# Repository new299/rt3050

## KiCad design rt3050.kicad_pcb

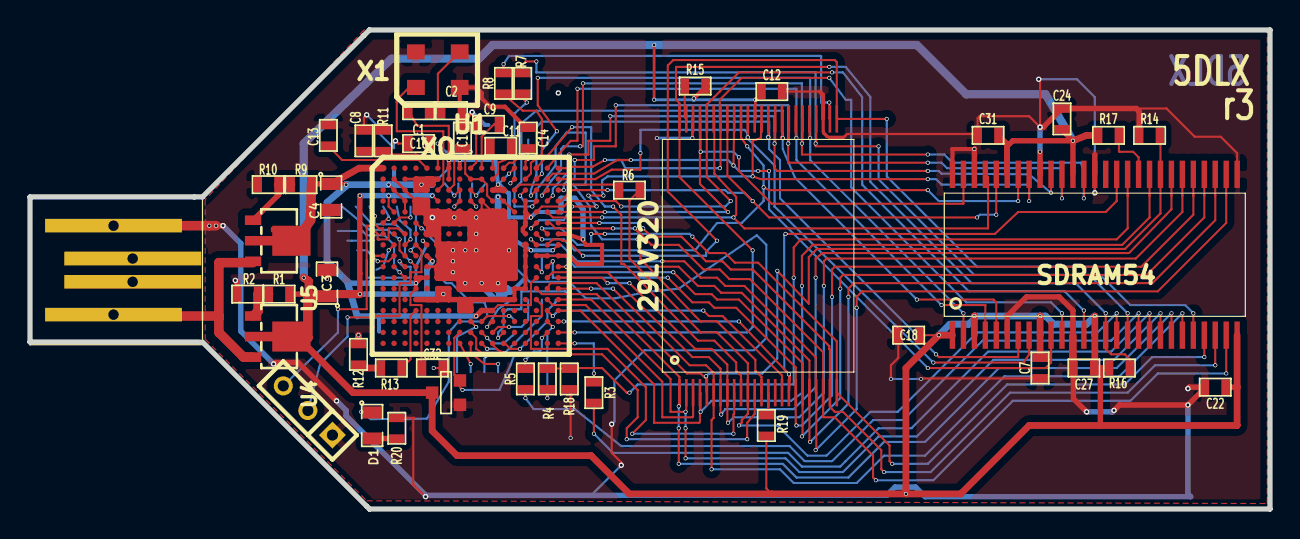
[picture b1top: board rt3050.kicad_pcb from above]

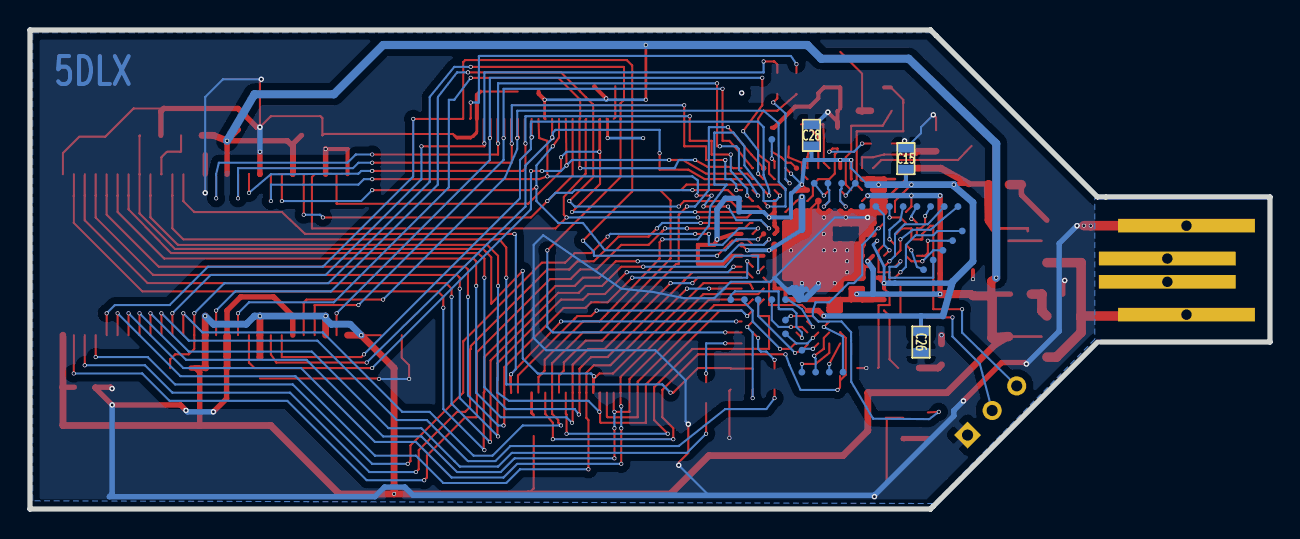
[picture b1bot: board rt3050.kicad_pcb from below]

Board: 2 copper layers, 90.6 x 35.0 mm, 60 parts (11 on the bottom side), 106 nets.

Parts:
C1, C2, C7, C8, C9, C11, C12, C13, C14, C15, C16, C17, C18, C22, C24, C26, C27, C28, C31, C32: C; SM0603
C3, C4: C; SM0805
D1: LED; SM0805
J1: USB; USBEDGE
K1: CONN_SERIAL; SIL-3
P1: CONN_JTAG; smpad6
P2: CONN_RF; smpad4
P3, P7: CONN_1; smpad1
P4: CONN_SERIAL2; smpad8
P5: CONN_SPI; smpad4
P6: CONN_2; smpad2
P8: CONN_USB; smpads5
R1, R2, R9, R10, R11, R12, R13, R14, R15, R16, R17, R18, R19, R20: R; SM0603
R3, R5, R6, R7, R8: 36; SM0603
R4: 100; SM0603
U1: RT3050; TFBGA289
U2: 29LV320; TSOP48
U3: SDRAM54; TSOP54
U4, U5: LM1117; SOT89
U6: AIC809; SOT23GDS
X1: XO; SMD3225

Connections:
+1.2V: C4.1, C15.1, C26.1, C28.1, C32.1, R9.1, U1.A1, U1.A7, U1.A8, U1.A13, U1.B3, U1.B4, U1.B5, U1.B6, U1.B7, U1.C2, U1.C4, U1.C5, U1.C11, U1.C12, U1.D3, U1.D14, U1.E3, U1.E14, U1.F14, U1.G14, U1.G17, U1.H5, U1.J15, U1.J16, U1.J17, U1.L4, U1.L5, U1.L15, U1.M4, U1.P10, U1.P11, U5.2
+3.3V: C3.1, C7.1, C12.1, C18.1, C22.1, C24.1, C27.1, C31.1, R1.1, R15.2, R16.2, R17.1, R19.2, U1.D6, U1.D12, U1.E2, U1.E13, U1.H14, U1.H17, U1.J5, U1.J14, U1.K14, U1.L14, U1.M6, U1.M7, U1.M13, U1.M14, U1.N4, U1.N5, U1.N6, U1.N7, U1.N8, U1.N9, U1.N10, U1.N11, U1.N12, U1.N13, U1.P8, U1.P9, U2.37, U3.1, U3.3, U3.9, U3.14, U3.27, U3.43, U3.49, U4.2, U6.D
+5V: J1.1, U4.3, U5.3
GND: C2.2, C3.2, C4.2, C7.2, C8.2, C12.2, C13.2, C14.2, C15.2, C16.2, C17.2, C18.2, C22.2, C24.2, C26.2, C27.2, C28.2, C31.2, C32.2, J1.4, K1.1, P1.6, R2.2, R10.2, R11.2, R12.2, R14.1, R18.2, R20.2, U1.B2, U1.C3, U1.D4, U1.D5, U1.D10, U1.E4, U1.E5, U1.E6, U1.E7, U1.E8, U1.E9, U1.E10, U1.E11, U1.E12, U1.F5, U1.F6, U1.F7, U1.F8, U1.F9, U1.F10, U1.F11, U1.F12, U1.F13, U1.G5, U1.G6, U1.G9, U1.G10, U1.G11, U1.G12, U1.G13, U1.H6, U1.H7, U1.H8, U1.H9, U1.H10, U1.H11, U1.H12, U1.H13, U1.J6, U1.J7, U1.J8, U1.J9, U1.J10, U1.J11, U1.J12, U1.J13, U1.K5, U1.K6, U1.K7, U1.K8, U1.K9, U1.K10, U1.K11, U1.K12, U1.K13, U1.L6, U1.L7, U1.L8, U1.L9, U1.L10, U1.L11, U1.L12, U1.L13, U1.M8, U1.M9, U1.M10, U1.M11, U1.M12, U2.27, U2.46, U3.6, U3.12, U3.28, U3.41, U3.46, U3.52, U3.54, U6.G, X1.2, X1.4
unnamed: P1.5, U1.R11
unnamed: P4.3, U1.F2
unnamed: P1.3, U1.U11
unnamed: P1.1, U1.T12
unnamed: P4.7, U1.K4
unnamed: K1.3, U1.G3
unnamed: U1.C6, X1.1
unnamed: P8.1, U1.H2
unnamed: P4.5, U1.F1
unnamed: D1.2, R20.1
unnamed: C1.2, U1.C7
unnamed: P8.3, U1.J2
unnamed: P7.1, U1.U10
unnamed: P4.8, U1.J3
unnamed: P5.4, U1.R9
unnamed: P4.2, U1.J4
unnamed: P4.4, U1.H3
unnamed: P8.2, U1.K3
unnamed: P1.2, U1.U12
unnamed: P8.4, U1.J1
unnamed: P5.2, U1.T9
unnamed: K1.2, U1.H4
unnamed: P4.6, U1.G1
unnamed: D1.1, U1.F4
unnamed: P1.4, U1.T11
unnamed: P6.1, U1.R10
unnamed: P8.5, U1.L3
unnamed: C1.1, C2.1, X1.3
unnamed: P5.3, U1.U8
unnamed: P5.1, U1.U9
unnamed: P6.2, U1.T10
unnamed: R9.2, R10.1, U5.1
unnamed: R1.2, R2.1, U4.1
unnamed: U1.A17, U2.42, U3.11
unnamed: U1.K15, U2.20, U3.30
unnamed: U1.M17, U2.6, U3.22
unnamed: U1.E16, U2.43, U3.51
unnamed: U1.B17, U2.38, U3.8
unnamed: U1.D15, U2.33, U3.5
unnamed: R8.1, U2.26
unnamed: U1.D16, U2.34, U3.45
unnamed: U1.F17, U2.23, U3.25
unnamed: U1.L16, U2.7, U3.34
unnamed: U1.K16, U2.18, U3.32
unnamed: U1.H16, U2.25, U3.23
unnamed: R15.1, U2.47
unnamed: U1.F15, U2.36, U3.47
unnamed: U1.P16, U2.16
unnamed: R8.2, U1.B14
unnamed: U1.B15, U2.29, U3.2
unnamed: U1.N16, U2.3
unnamed: U1.N15, U2.9
unnamed: U1.E17, U2.45, U3.53
unnamed: R3.2, U1.U17
unnamed: R5.2, U1.T16
unnamed: R4.2, U1.R16
unnamed: U1.G15, U2.39, U3.48
unnamed: R6.2, U1.C13
unnamed: R7.2, U1.B13
unnamed: R3.1, U3.19
unnamed: R17.2, U3.37
unnamed: U1.A15, U2.10
unnamed: U1.C14, U2.13
unnamed: P3.1, U1.A14
unnamed: U1.A16, U2.31, U3.4
unnamed: U1.C15, U2.35, U3.7
unnamed: U1.B16, U2.40, U3.10
unnamed: U1.E15, U2.44, U3.13
unnamed: U1.G16, U2.24, U3.24
unnamed: U1.F16, U2.22, U3.26
unnamed: U1.K17, U2.19, U3.31
unnamed: U1.L17, U2.8, U3.33
unnamed: U1.R17, U2.17, U3.39
unnamed: R4.1, R18.1, U3.38
unnamed: U1.D17, U2.41, U3.50
unnamed: R14.2, U1.M16, U2.5, U3.35
unnamed: R5.1, U3.18
unnamed: U1.C16, U2.30, U3.42
unnamed: R7.1, U2.28, U3.17
unnamed: U1.N17, U2.2, U3.20
unnamed: R16.1, U1.T17, U2.48, U3.15
unnamed: R19.1, U2.14
unnamed: U1.P17, U2.4, U3.36
unnamed: U1.M15, U2.1, U3.21
unnamed: U1.C17, U2.32, U3.44
unnamed: R6.1, U2.11, U3.16
unnamed: U1.H15, U2.21, U3.29
unnamed: R12.1, R13.2
unnamed: R13.1, U1.P4
unnamed: C9.2, U1.A9
unnamed: C8.1, R11.1, U1.A6
unnamed: C11.2, U1.B11
unnamed: C13.1, U1.A5
unnamed: P2.2, U1.D8
unnamed: P2.4, U1.C9
unnamed: P2.3, U1.D9
unnamed: P2.1, U1.C8
unnamed: C9.1, U1.A10
unnamed: C11.1, U1.A11
unnamed: C14.1, U1.A12
unnamed: C16.1, C17.1, U1.B9, U1.B10, U1.D11
RST: U1.T8, U2.12, U6.S

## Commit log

2014-09-02 starting DRC check
2014-09-03 upgraded kicad
2014-09-03 added project file
2014-09-03 more cleanup
2014-09-04 as sent for r1 to hackvana.
2014-09-06 r2 for fab
2014-09-13 hackvana final
2014-11-07 updated component values
